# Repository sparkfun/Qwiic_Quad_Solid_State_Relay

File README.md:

SparkFun Qwiic Quad Solid State Relay Kit
========================================

[*SparkFun Qwiic Dual Solid State Relay Kit (KIT-16833)*](https://www.sparkfun.com/products/16833)

The SparkFun Quad Solid State Relay Kit comes with four solid state relays you can assemble on to a single board allowing you to control all of them from a microcontroller via I<sup>2</sup>C with the Qwiic Ecosystem. The relays are rated for 40A @28-380VAC allowing you to harness some serious high voltage power from simple I<sup>2</sup>C commands from your favorite microcontroller.

The Qwiic Quad Solid State Relay comes requires some basic assembly to attach the relays and connect your AC load. It uses the simple [Qwiic interface](https://www.sparkfun.com/qwiic). No soldering, no voltage translation, no figuring out which pin is SDA or SCL, just plug and go!

**Note:** Controlling high voltage (110/220VAC) requires certain precautions. A beginner can do it but if you're wary of working with high voltage, you may want to consider the pre-made [IoT Power Relay](https://www.sparkfun.com/products/14236). It's not controlled via I<sup>2</sup>C but the IoT Power Relay contains shielding to prevent accidental shock.

Repository Contents
-------------------

* **/Documentation** - Data sheets, additional product information
* **/Firmware** - Latest firmware
* **/Hardware** - Eagle design files (.brd, .sch)
* **/Production** - Production panel files (.brd)

Documentation
--------------
* **[SparkFun Qwiic Relay Arduino Library](https://github.com/sparkfun/SparkFun_Qwiic_Relay_Arduino_Library)** - Arduino library for SparkFun Qwiic Relay boards.
* **[Hookup Guide](https://learn.sparkfun.com/tutorials/sparkfun-qwiic-quad-solid-state-relay-kit-hookup-guide)** - Basic hookup guide for the Qwiic Dual Solid State Relay.

Product Versions
----------------
* [KIT-16833](https://www.sparkfun.com/products/16810)- Initial release of the Qwiic Quad Solid State Relay Kit.

License Information
-------------------

This product is _**open source**_! 

Please review the LICENSE.md file for license information. 

If you have any questions or concerns on licensing, please contact technical support on our [SparkFun forums](https://forum.sparkfun.com/viewforum.php?f=152).

Distributed as-is; no warranty is given.

- Your friends at SparkFun.

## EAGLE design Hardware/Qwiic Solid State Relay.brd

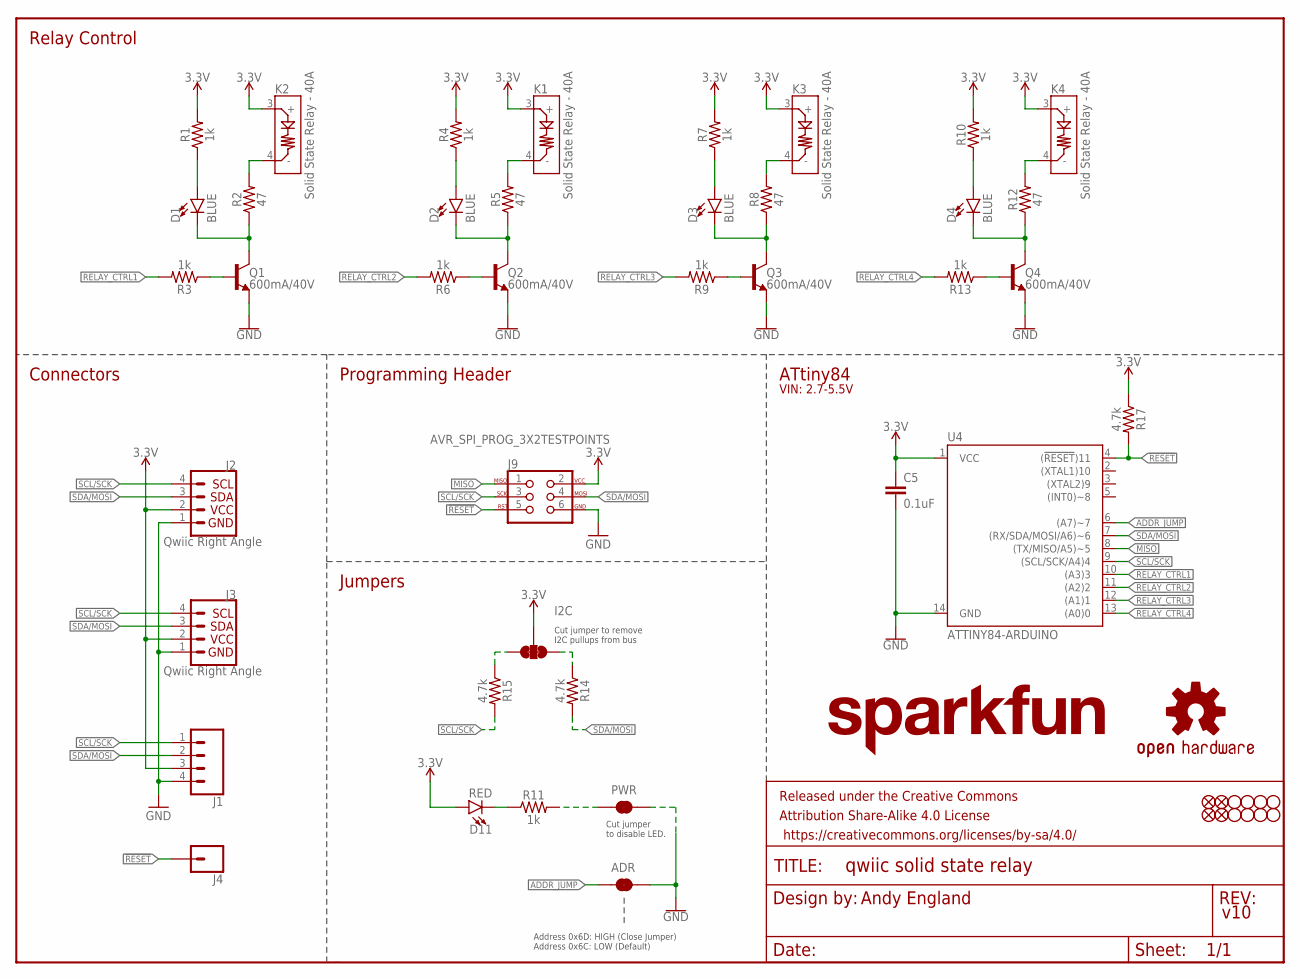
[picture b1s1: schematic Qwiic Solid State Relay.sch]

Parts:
ADR: JUMPER-SMT_2_NC_TRACE_SILK; SMT-JUMPER_2_NC_TRACE_SILK
C5: 0.1uF; 0603
D1, D2, D3, D4: BLUE; LED-0603
D11: RED; LED-0603
FD1, FD2, FD3, FD4: FIDUCIAL1X2; FIDUCIAL-1X2
FRAME1: FRAME-LETTER; CREATIVE_COMMONS
I2C: JUMPER-SMT_3_2-NC_TRACE_SILK; SMT-JUMPER_3_2-NC_TRACE_SILK
J1: CONN_041X04_NO_SILK; 1X04_NO_SILK
J2, J3: Qwiic Right Angle; JST04_1MM_RA
J4: CONN_01PTH_NO_SILK_YES_STOP; 1X01_NO_SILK
J9: AVR_SPI_PROG_3X2TESTPOINTS; 2X3_TEST_POINTS
JP1, JP2, JP3, JP4, JP5, JP6, JP7, JP8: STAND-OFF
K1, K2, K3, K4: Solid State Relay - 40A; SSR-40DA-H
LOGO1: SFE_LOGO_NAME1_INCH; SFE_LOGO_NAME_1
LOGO2: OSHW-LOGOS; OSHW-LOGO-S
PWR: JUMPER-SMT_2_NC_TRACE_SILK; SMT-JUMPER_2_NC_TRACE_SILK
Q1, Q2, Q3, Q4: 600mA/40V; SOT23-3
R1, R3, R4, R6, R7, R9, R10, R11, R13: 1k; 0603
R2, R5, R8, R12: 47; 0603
R14, R15, R17: 4.7k; 0603
U4: ATTINY84-ARDUINO; SO14

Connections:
3.3V: C5.1, D11.A, I2C.2, J1.3, J2.2, J3.2, J9.2, K1.3 (+), K2.3 (+), K3.3 (+), K4.3 (+), R1.2, R4.2, R7.2, R10.2, R17.1, U4.1 (VCC)
!RESET: J4.1, J9.5, R17.2, U4.4 ((!RESET!)11)
ADDR_JUMP: ADR.1, U4.6 ((A7)~7)
GND: ADR.2, C5.2, J1.4, J2.1, J3.1, J9.6, PWR.1, Q1.2 (E), Q2.2 (E), Q3.2 (E), Q4.2 (E), U4.14 (GND)
MISO: J9.1, U4.8 ((TX/MISO/A5)~5)
unnamed: D2.C, Q2.3 (C), R5.1
unnamed: D1.C, Q1.3 (C), R2.1
unnamed: K1.4 (-), R5.2
unnamed: D2.A, R4.1
unnamed: D3.C, Q3.3 (C), R8.1
unnamed: K3.4 (-), R8.2
unnamed: D1.A, R1.1
unnamed: D3.A, R7.1
unnamed: D4.C, Q4.3 (C), R12.1
unnamed: K2.4 (-), R2.2
unnamed: K4.4 (-), R12.2
unnamed: D4.A, R10.1
unnamed: D11.C, R11.1
unnamed: PWR.2, R11.2
unnamed: I2C.3, R15.1
unnamed: I2C.1, R14.1
OPTO_1: Q1.1 (B), R3.1
OPTO_2: Q2.1 (B), R6.1
OPTO_3: Q3.1 (B), R9.1
OPTO_4: Q4.1 (B), R13.1
RELAY_CTRL1: R3.2, U4.10 ((A3)3)
RELAY_CTRL2: R6.2, U4.11 ((A2)2)
RELAY_CTRL3: R9.2, U4.12 ((A1)1)
RELAY_CTRL4: R13.2, U4.13 ((A0)0)
SCL/SCK: J1.1, J2.4, J3.4, J9.3, R15.2, U4.9 ((SCL/SCK/A4)4)
SDA/MOSI: J1.2, J2.3, J3.3, J9.4, R14.2, U4.7 ((RX/SDA/MOSI/A6)~6)

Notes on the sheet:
Andy England
v10
Connectors
ATtiny84
Programming Header
Address 0x6D: HIGH (Close Jumper) Address 0x6C: LOW (Default)
Cut jumper to disable LED.
Jumpers
Relay Control
Cut jumper to remove I2C pullups from bus
VIN: 2.7-5.5V

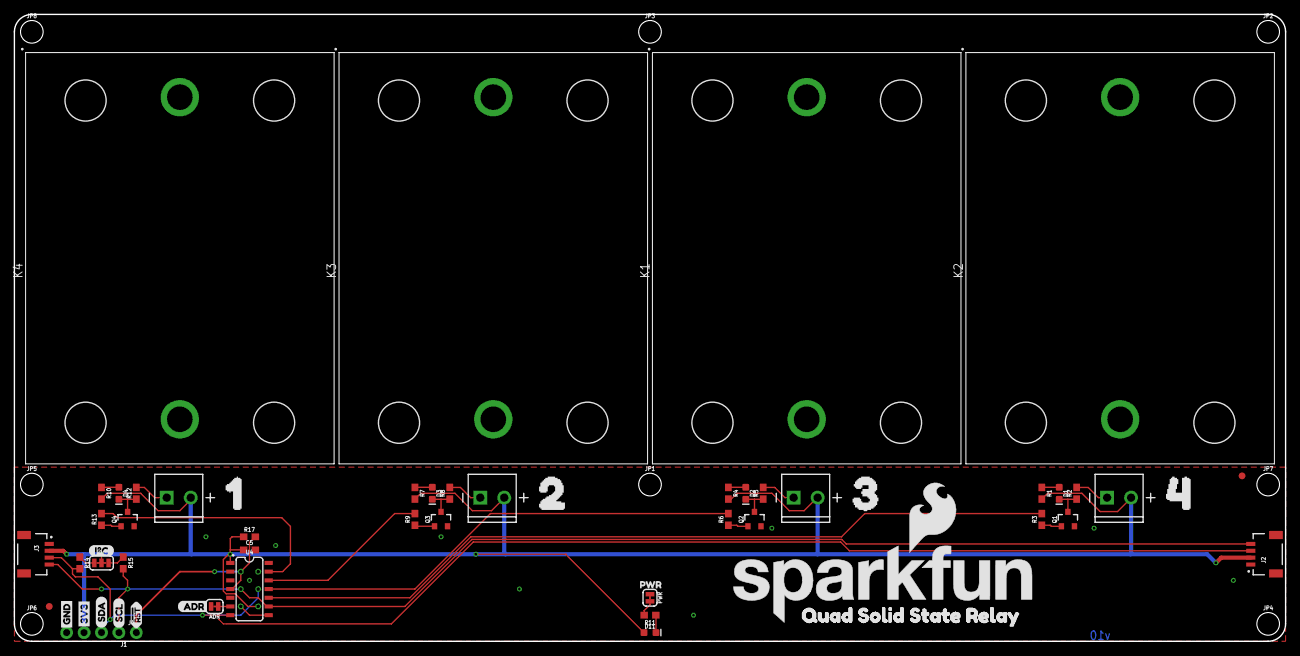
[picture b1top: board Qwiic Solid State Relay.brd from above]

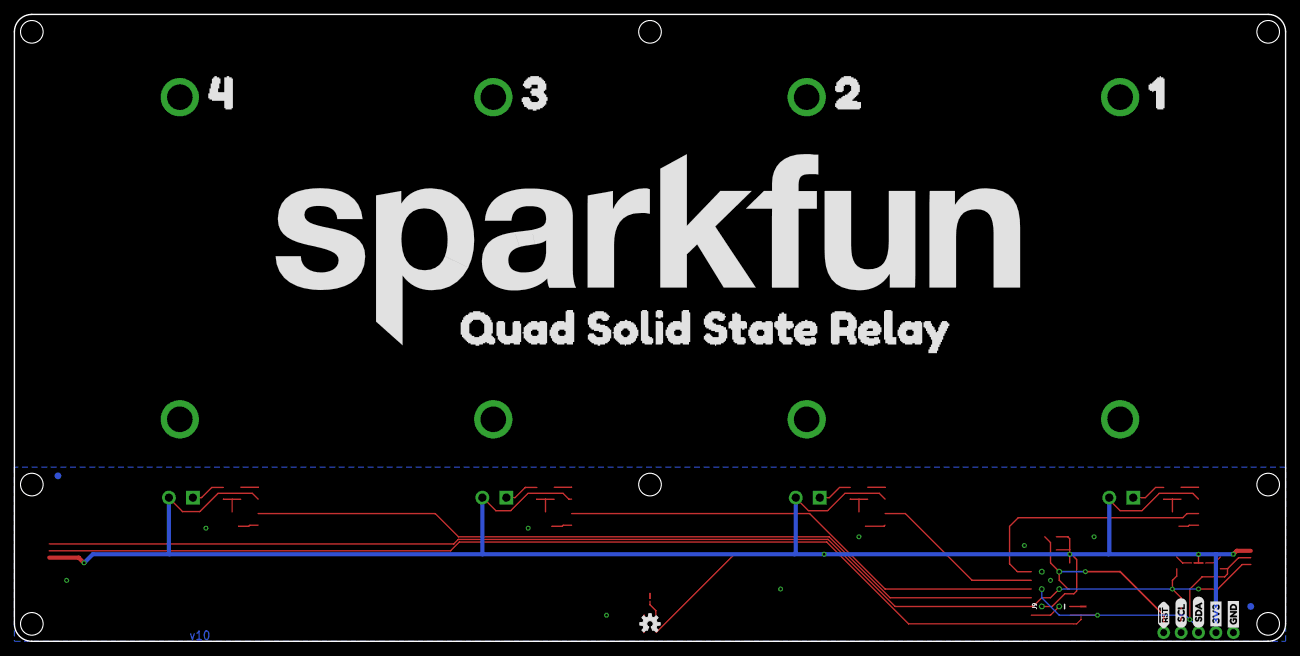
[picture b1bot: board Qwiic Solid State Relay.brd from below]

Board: 2 copper layers, 185.4 x 91.4 mm, 79 parts (15 on the bottom side), 31 nets.

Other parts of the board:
U$1: SFE_LOGO_NAME_FLAME_.4
U$2, U$3, U$4: QUAD_SOLID_STATE_RELAY0
U$5, U$9: 11
U$6, U$10: 22
U$7, U$11: 33
U$8, U$12: 44
U$13, U$14: GND_P
U$15: I2C
U$16, U$17: 3V3_P
U$18, U$19: SCL_IO
U$20, U$21: SDA_IO
U$22: PWR_TO
U$23: ADR3
U$24, U$25: !RST_I

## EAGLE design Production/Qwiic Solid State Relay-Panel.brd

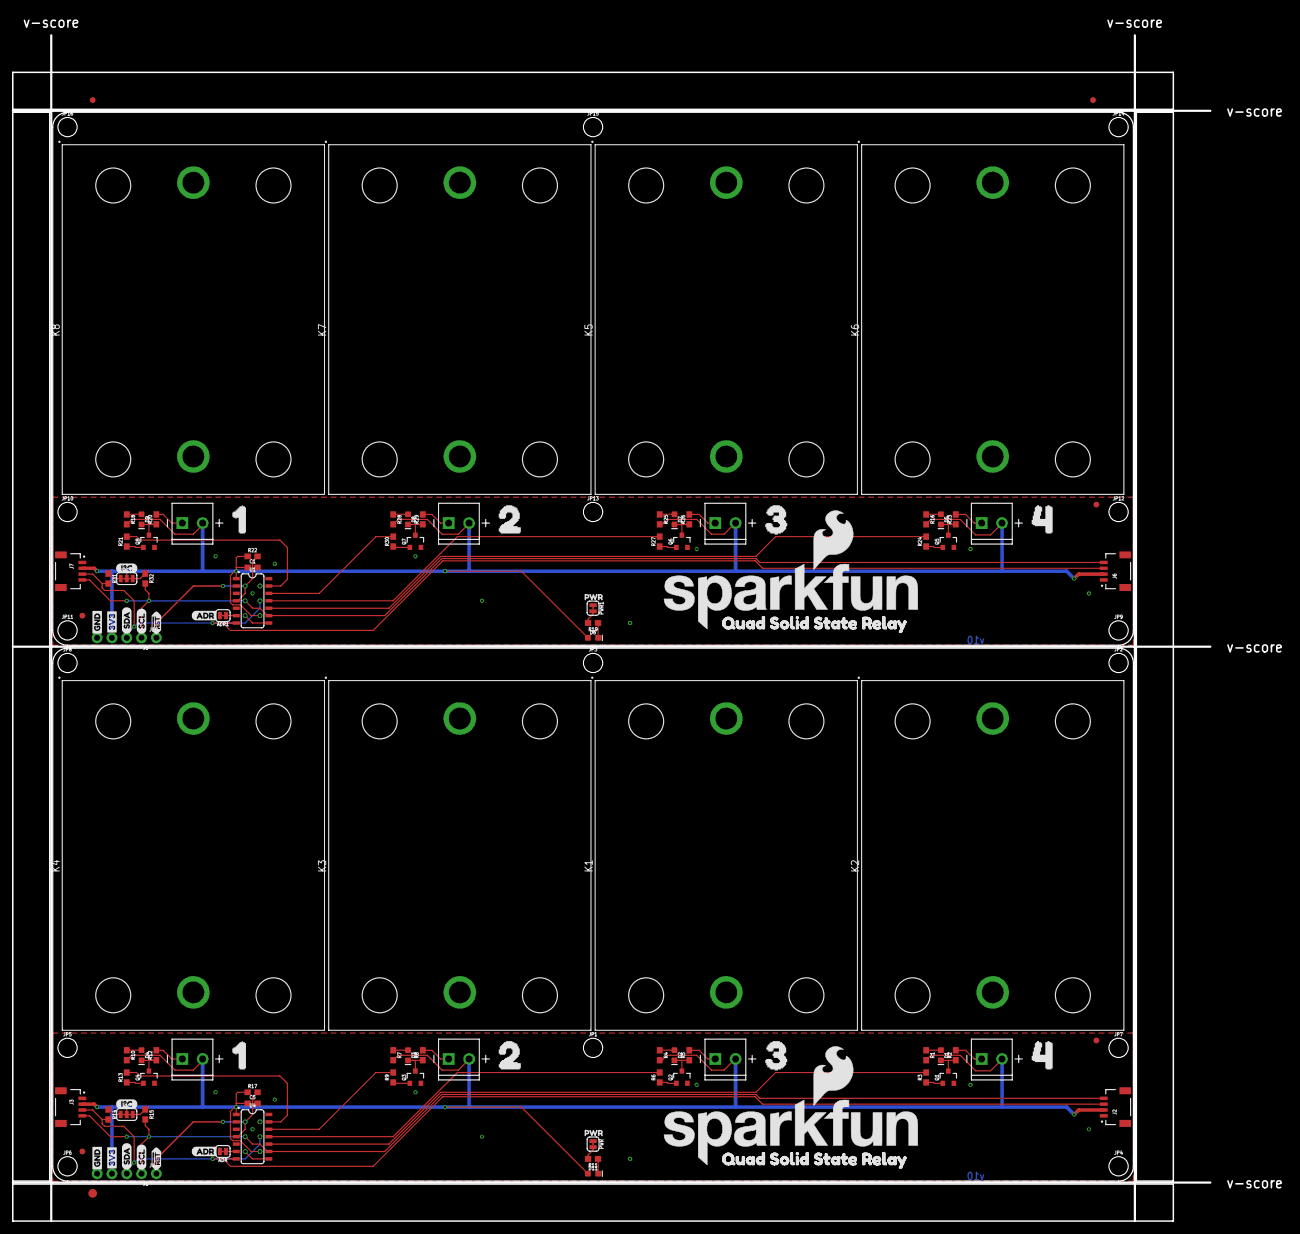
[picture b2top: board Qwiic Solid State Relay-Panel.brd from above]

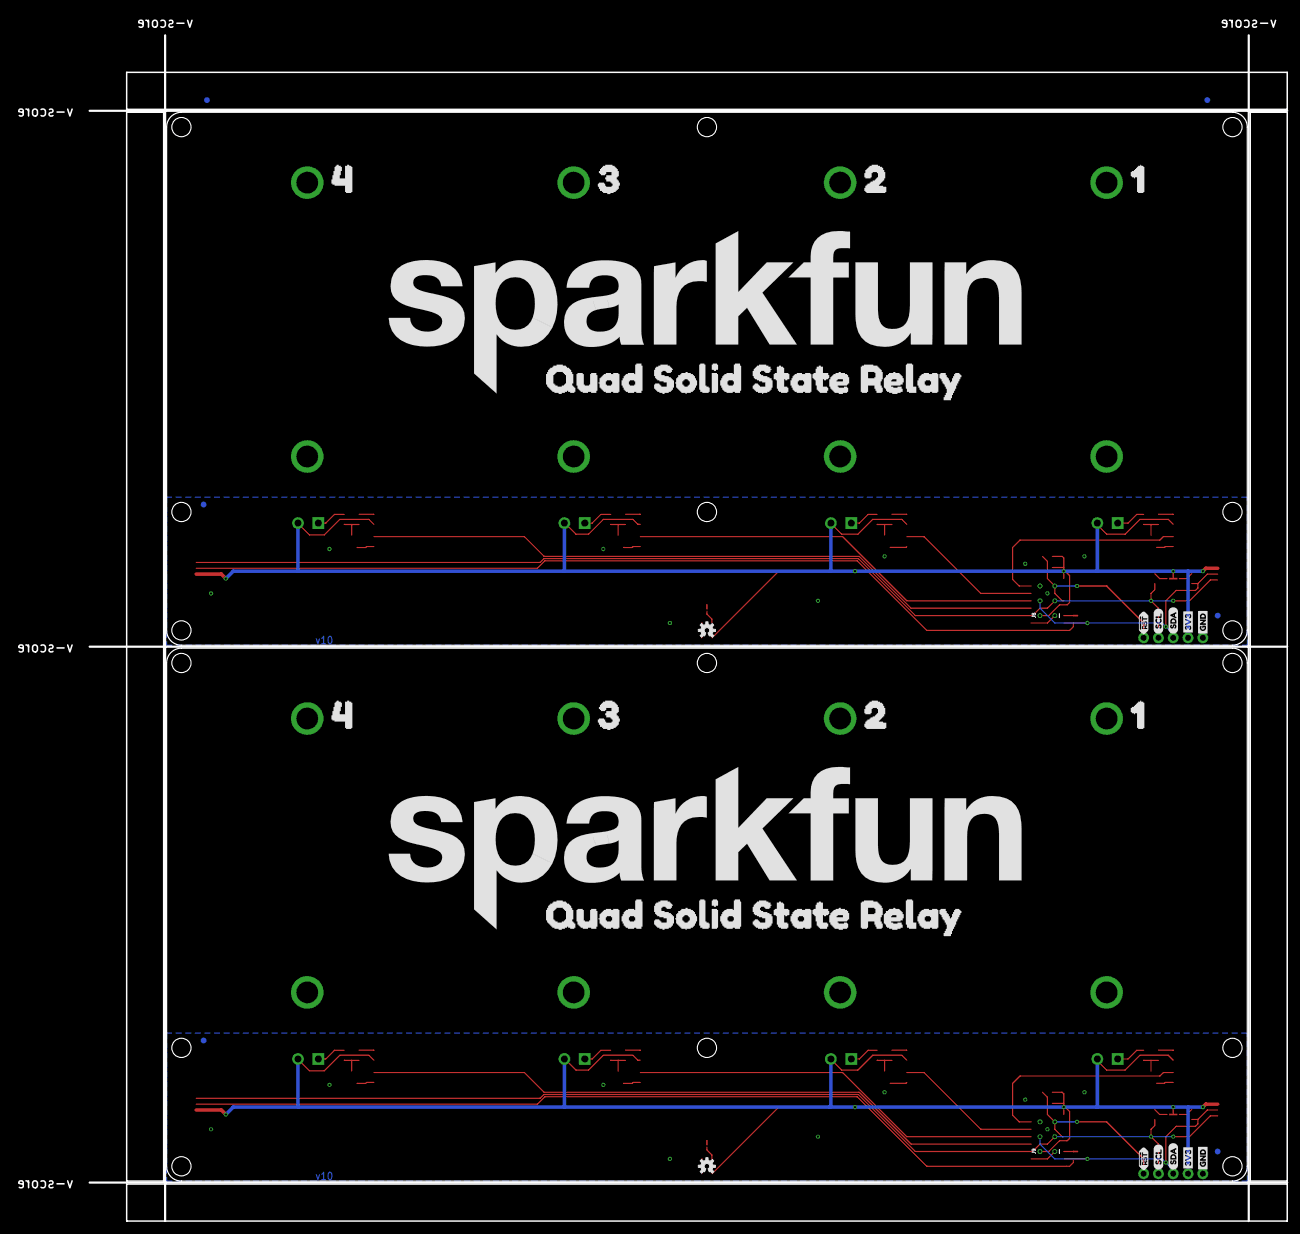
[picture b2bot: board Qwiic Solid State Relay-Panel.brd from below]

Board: 2 copper layers, 218.7 x 207.3 mm, 161 parts (32 on the bottom side), 62 nets.

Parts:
ADR, ADR1: JUMPER-SMT_2_NC_TRACE_SILK; SMT-JUMPER_2_NC_TRACE_SILK
C1, C5: 0.1uF; 0603
D1, D2, D3, D4, D5, D7, D8, D9: BLUE; LED-0603
D6, D11: RED; LED-0603
E$1, E$2, E$3, E$4: FIDUCIAL-1X2
E$5: FIDUCIAL-1.5X3
FD1, FD2, FD3, FD4, FD5, FD6, FD7, FD8: FIDUCIAL1X2; FIDUCIAL-1X2
I2C, I2C1: JUMPER-SMT_3_2-NC_TRACE_SILK; SMT-JUMPER_3_2-NC_TRACE_SILK
J1, J5: 1X04_NO_SILK
J2, J3, J6, J7: Qwiic Right Angle; JST04_1MM_RA
J4, J10: 1X01_NO_SILK
J8, J9: AVR_SPI_PROG_3X2TESTPOINTS; 2X3_TEST_POINTS
JP1, JP2, JP3, JP4, JP5, JP6, JP7, JP8, JP9, JP10, JP11, JP12, JP13, JP14, JP15, JP16: STAND-OFF
K1, K2, K3, K4, K5, K6, K7, K8: Solid State Relay - 40A; SSR-40DA-H
LOGO1, LOGO4: SFE_LOGO_NAME1_INCH; SFE_LOGO_NAME_1
LOGO2, LOGO3: OSHW-LOGOS; OSHW-LOGO-S
PWR, PWR1: JUMPER-SMT_2_NC_TRACE_SILK; SMT-JUMPER_2_NC_TRACE_SILK
Q1, Q2, Q3, Q4, Q5, Q6, Q7, Q8: 600mA/40V; SOT23-3
R1, R3, R4, R6, R7, R9, R10, R11, R13, R16, R18, R19, R21, R24, R25, R27, R28, R30: 1k; 0603
R2, R5, R8, R12, R20, R23, R26, R29: 47; 0603
R14, R15, R17, R22, R31, R32: 4.7k; 0603
U1, U4: ATTINY84-ARDUINO; SO14
U$1, U$26: SFE_LOGO_NAME_FLAME_.4
U$2, U$3, U$4, U$27, U$28, U$29: QUAD_SOLID_STATE_RELAY0
U$5, U$9, U$30, U$34: 11
U$6, U$10, U$31, U$35: 22
U$7, U$11, U$32, U$36: 33
U$8, U$12, U$33, U$37: 44
U$13, U$14, U$38, U$39: GND_P
U$15, U$40: I2C
U$16, U$17, U$41, U$42: 3V3_P
U$18, U$19, U$43, U$44: SCL_IO
U$20, U$21, U$45, U$46: SDA_IO
U$22, U$47: PWR_TO
U$23, U$48: ADR3
U$24, U$25, U$49, U$50: !RST_I

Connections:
3.3V: C5.1, D11.A, I2C.2, J1.3, J2.2, J3.2, J9.2, K1.2, K2.2, K3.2, K4.2, R1.2, R4.2, R7.2, R10.2, R17.1, U4.1
3.3V1: C1.1, D6.A, I2C1.2, J5.3, J6.2, J7.2, J8.2, K5.2, K6.2, K7.2, K8.2, R16.2, R18.2, R22.1, R25.2, R28.2, U1.1
!RESET: J4.1, J9.5, R17.2, U4.4
!RESET1: J8.5, J10.1, R22.2, U1.4
ADDR_JUMP: ADR.1, U4.6
ADDR_JUMP1: ADR1.1, U1.6
GND: ADR.2, C5.2, J1.4, J2.1, J3.1, J9.6, PWR.1, Q1.2, Q2.2, Q3.2, Q4.2, U4.14
GND1: ADR1.2, C1.2, J5.4, J6.1, J7.1, J8.6, PWR1.1, Q5.2, Q6.2, Q7.2, Q8.2, U1.14
MISO: J9.1, U4.8
MISO1: J8.1, U1.8
unnamed: D2.C, Q2.3, R5.1
unnamed: D1.C, Q1.3, R2.1
unnamed: K1.1, R5.2
unnamed: D2.A, R4.1
unnamed: D3.C, Q3.3, R8.1
unnamed: K3.1, R8.2
unnamed: D1.A, R1.1
unnamed: D3.A, R7.1
unnamed: D4.C, Q4.3, R12.1
unnamed: K2.1, R2.2
unnamed: K4.1, R12.2
unnamed: D4.A, R10.1
unnamed: D11.C, R11.1
unnamed: PWR.2, R11.2
unnamed: I2C.3, R15.1
unnamed: I2C.1, R14.1
unnamed: D6.C, R19.1
unnamed: PWR1.2, R19.2
unnamed: D5.C, Q5.3, R23.1
unnamed: K6.1, R23.2
unnamed: D5.A, R16.1
unnamed: D7.C, Q6.3, R26.1
unnamed: K5.1, R26.2
unnamed: D7.A, R25.1
unnamed: D8.C, Q7.3, R29.1
unnamed: K7.1, R29.2
unnamed: D8.A, R28.1
unnamed: D9.C, Q8.3, R20.1
unnamed: K8.1, R20.2
unnamed: D9.A, R18.1
unnamed: I2C1.3, R32.1
unnamed: I2C1.1, R31.1
OPTO_1: Q1.1, R3.1
OPTO_2: Q2.1, R6.1
OPTO_3: Q3.1, R9.1
OPTO_4: Q4.1, R13.1
OPTO_5: Q5.1, R24.1
OPTO_6: Q6.1, R27.1
OPTO_7: Q7.1, R30.1
OPTO_8: Q8.1, R21.1
RELAY_CTRL1: R3.2, U4.10
RELAY_CTRL2: R6.2, U4.11
RELAY_CTRL3: R9.2, U4.12
RELAY_CTRL4: R13.2, U4.13
RELAY_CTRL5: R24.2, U1.10
RELAY_CTRL6: R27.2, U1.11
RELAY_CTRL7: R30.2, U1.12
RELAY_CTRL8: R21.2, U1.13
SCL/SCK: J1.1, J2.4, J3.4, J9.3, R15.2, U4.9
SCL/SCK1: J5.1, J6.4, J7.4, J8.3, R32.2, U1.9
SDA/MOSI: J1.2, J2.3, J3.3, J9.4, R14.2, U4.7
SDA/MOSI1: J5.2, J6.3, J7.3, J8.4, R31.2, U1.7

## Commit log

2020-05-20 adding silk
2020-05-22 fixing overlap error, wire stub
2020-05-26 updating for reds after design review, checklist
2020-05-26 forgot to save brd file for previous commit
2020-05-29 adding panel
2020-06-23 switching pin labels around to match SSR
2020-07-07 Update Readme
    Adding product/documentation links to the readme. Photo still needed.
2020-07-09 updating firmware for release
2020-07-14 finalizing changes to SlowPWM, 120Hz
2020-07-14 updating schematic address note
2020-07-14 Update README
    fixing minor errors and updating photo.
2020-07-14 updating so SlowPWM always turns off
2020-07-15 fixing SlowPWM relay start condition that would cause things to turn off
2020-12-29 Add Firmware version and fix PWM bug
    - Add Firmware version request register (0x30)
    - Remove special status response from requestEvent() as it's not
    obvious and not documented.
    - Collapse similar code blocks that handles relays 1 through 4
    rather than blocks that handle a single relay at a time.
    - Use relayPin array to lookup pins in all cases.
2020-12-29 Add Firmware test
2020-12-31 Handle PWM 0.0 command
    Handles case where if you stop the pulse when HIGH, it'll stay high.
    With this change, a PWM of 0.0 means turn off and clear the pwmValue.
2023-12-19 Better location for loading into Arduino IDE

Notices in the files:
parts and their libraries:
SparkFun-Capacitors: Licensing: Creative Commons ShareAlike 4.0 International - https://creativecommons.org/licenses/by-sa/4.0
SparkFun-Aesthetics: Released under the Creative Commons Attribution Share-Alike 4.0 License
SparkFun-Aesthetics: https://creativecommons.org/licenses/by-sa/4.0
